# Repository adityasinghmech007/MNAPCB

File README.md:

# STM32-Based Motor Control PCB

## 📌 Overview

This project is a custom-designed 2-layer motor control PCB developed for embedded motion control and automation applications. The board integrates an STM32 microcontroller, motor driver circuitry, INA226 current sensing, and onboard power management for efficient and reliable motor control.

The PCB was designed to support real-time motor actuation, current monitoring, and embedded control workflows for robotics and mechatronics systems.

---

## 🚀 Features

* STM32-based embedded control system
* Integrated motor driver interface for DC/Stepper motor control
* INA226 current and voltage monitoring
* Onboard DC power regulation circuitry
* Multi-voltage power distribution architecture
* 2-layer PCB optimized for compact routing and manufacturability
* Support for sensor interfacing and external peripherals
* Designed for rapid prototyping and embedded testing applications

---

## 🔧 Hardware Components

### Microcontroller

* STM32 MCU for real-time motor control and peripheral interfacing

### Current Sensing

* INA226 current/voltage monitoring IC
* I2C communication interface

### Motor Control

* Motor driver integration for controlling motors
* PWM and direction-based control signals

### Power Management

* DC-DC conversion stages for generating required operating voltages
* Power filtering and decoupling circuitry
* Separate logic and motor power domains

---

## 🛠️ PCB Design Details

* 2-layer PCB design
* Optimized power and signal routing
* Ground plane implementation for noise reduction
* Compact component placement for efficient thermal and electrical performance
* Designed using standard PCB CAD tools

---

## 💻 Firmware & Embedded Features

* STM32 HAL-based firmware development
* PWM motor control
* Current monitoring using INA226
* GPIO, I2C, UART, and timer peripheral integration
* Real-time control and debugging support

---

## 📷 Project Highlights

* Complete schematic and PCB design from scratch
* Integrated power electronics and embedded control on a single board
* Focus on reliability, modularity, and rapid hardware iteration
* Suitable for robotics, automation, and mechatronics applications

---

## 🔩 Applications

* Robotics platforms
* Motor control systems
* Embedded automation
* Mechatronics prototyping
* Industrial testing systems

---

## 📚 Technologies Used

* STM32
* Embedded C
* PCB Design
* Power Electronics
* INA226
* Motor Drivers
* I2C Communication
* PWM Control

---

Built with a strong focus on practical embedded engineering, hardware integration, and real-world motion control applications.

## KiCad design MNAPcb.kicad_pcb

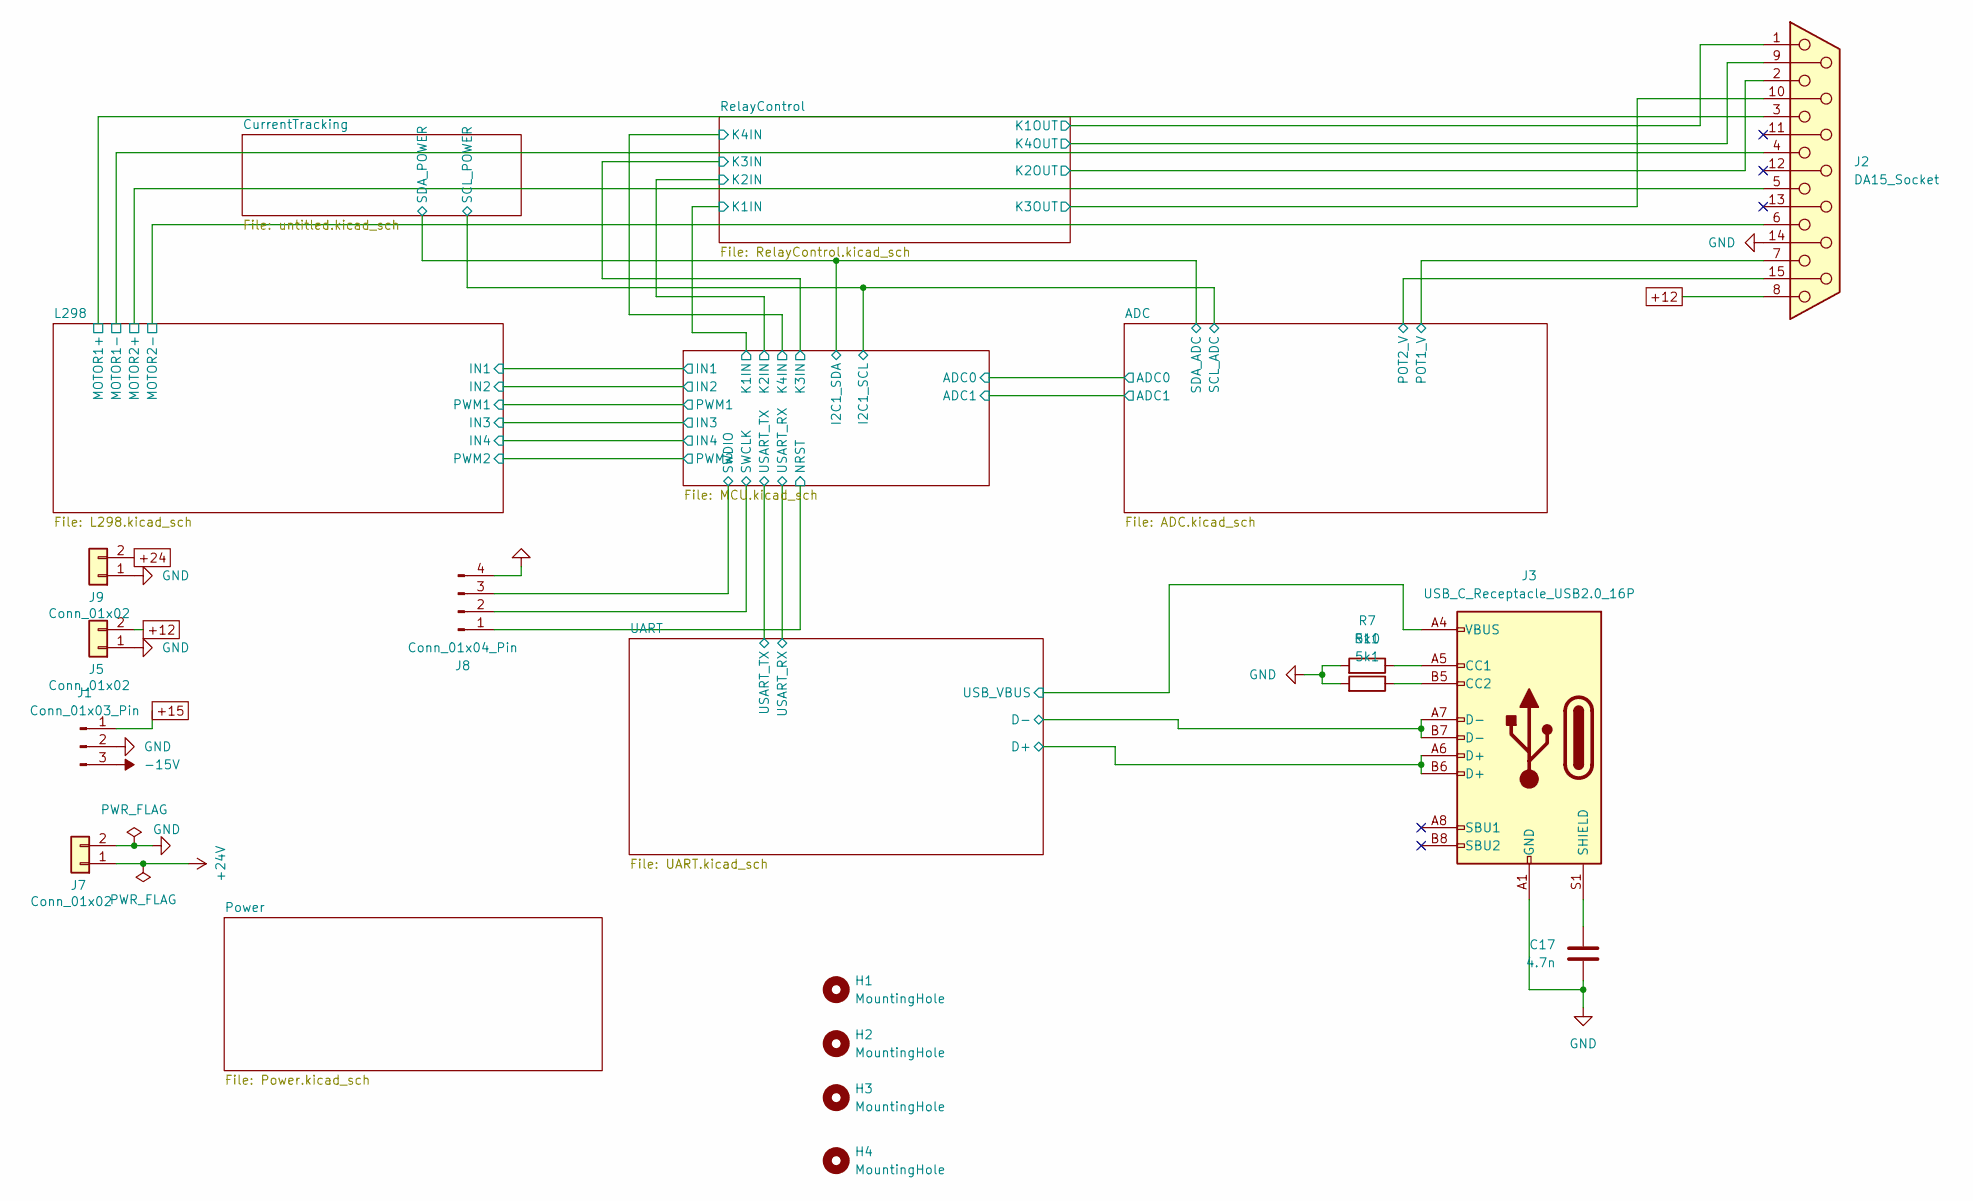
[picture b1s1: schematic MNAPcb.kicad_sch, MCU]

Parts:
C17: 4.7n; C_0805_2012Metric_Pad1.18x1.45mm_HandSolder
H1, H2, H3, H4: MountingHole; MountingHole_3.2mm_M3_DIN965
J1: Conn_01x03_Pin; Molex_KK-254_AE-6410-03A_1x03_P2.54mm_Vertical
J2: DA15_Socket; DSUB-15_Socket_Horizontal_P2.77x2.54mm_EdgePinOffset9.40mm
J3: USB_C_Receptacle_USB2.0_16P; USB_C_Receptacle_Palconn_UTC16-G
J5, J7, J9: Conn_01x02; TE_826576-2_1x02_P3.96mm_Vertical
J8: Conn_01x04_Pin; JST_EH_B4B-EH-A_1x04_P2.50mm_Vertical
R7, R10: 5k1; R_0805_2012Metric_Pad1.20x1.40mm_HandSolder

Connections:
+12: J2.8, J5.2; also elsewhere on the board
+15: J1.1; also elsewhere on the board
+24: J9.2; also elsewhere on the board
+24V: J7.1; also elsewhere on the board
-15V: J1.3; also elsewhere on the board
/ADC/POT1_V: J2.7; also elsewhere on the board
/ADC/POT2_V: J2.15; also elsewhere on the board
/L298/MOTOR1+: J2.3; also elsewhere on the board
/L298/MOTOR1-: J2.4; also elsewhere on the board
/L298/MOTOR2+: J2.5; also elsewhere on the board
/L298/MOTOR2-: J2.6; also elsewhere on the board
/MCU/NRST: J8.1; also elsewhere on the board
/MCU/SWCLK: J8.2; also elsewhere on the board
/MCU/SWDIO: J8.3; also elsewhere on the board
/RelayControl/K1OUT: J2.1; also elsewhere on the board
/RelayControl/K2OUT: J2.2; also elsewhere on the board
/RelayControl/K3OUT: J2.10; also elsewhere on the board
/RelayControl/K4OUT: J2.9; also elsewhere on the board
/UART/D+: J3.A6 (D+), J3.B6 (D+); also elsewhere on the board
/UART/D-: J3.A7 (D-), J3.B7 (D-); also elsewhere on the board
/UART/USB_VBUS: J3.A4 (VBUS), J3.A9 (VBUS), J3.B4 (VBUS), J3.B9 (VBUS); also elsewhere on the board
GND: C17.2, J1.2, J2.14, J3.A1 (GND), J3.A12 (GND), J3.B1 (GND), J3.B12 (GND), J5.1, J7.2, J8.4, J9.1, R7.2, R10.2; also elsewhere on the board
unnamed: J3.A5 (CC1), R7.1
unnamed: J3.B5 (CC2), R10.1
unnamed: C17.1, J3.S1 (SHIELD)

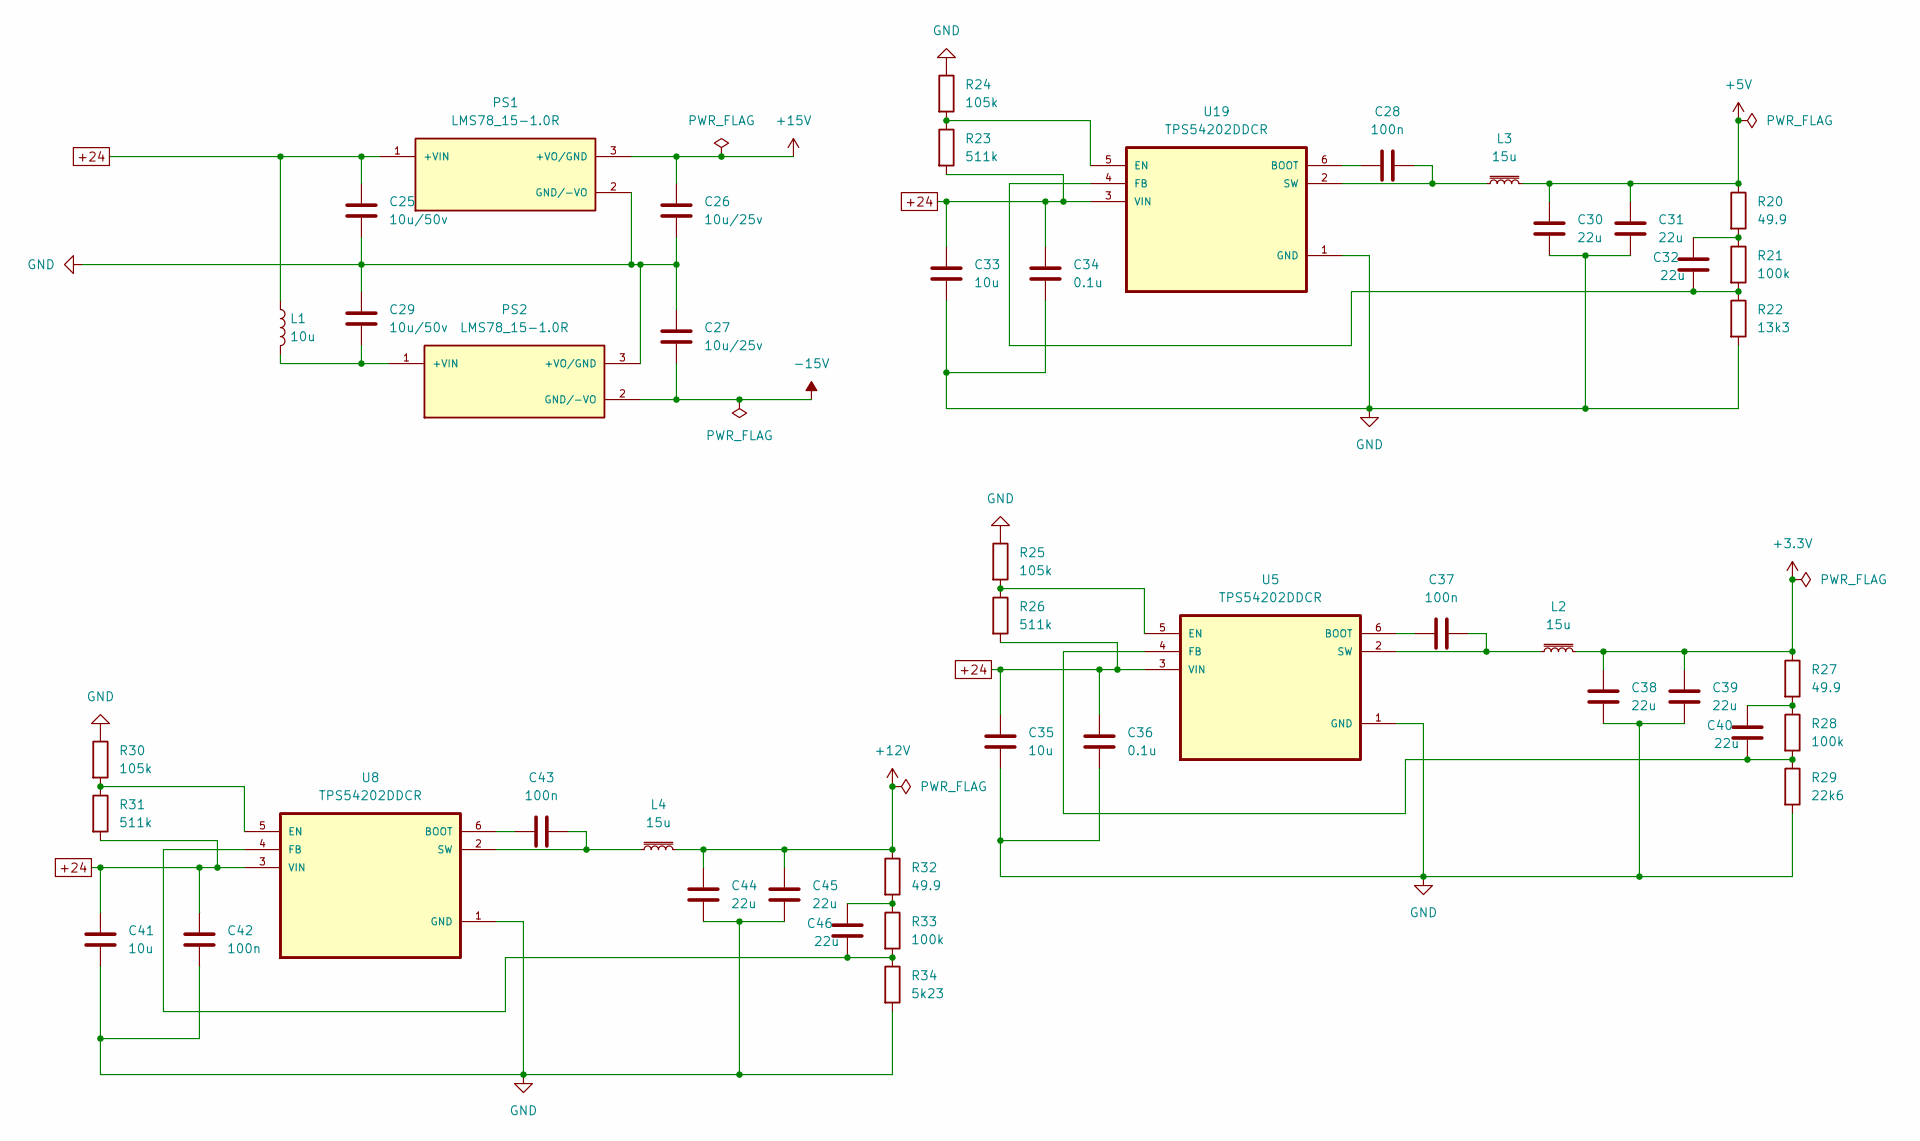
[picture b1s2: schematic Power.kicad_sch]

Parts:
C25, C29: 10u/50v; C_1210_3225Metric_Pad1.33x2.70mm_HandSolder
C26, C27: 10u/25v; C_1210_3225Metric_Pad1.33x2.70mm_HandSolder
C28, C37, C42, C43: 100n; C_0805_2012Metric_Pad1.18x1.45mm_HandSolder
C30, C31, C32, C38, C39, C40, C44, C45, C46: 22u; C_1210_3225Metric_Pad1.33x2.70mm_HandSolder
C33, C35, C41: 10u; C_1206_3216Metric_Pad1.33x1.80mm_HandSolder
C34, C36: 0.1u; C_0805_2012Metric_Pad1.18x1.45mm_HandSolder
L1: 10u; L_1210_3225Metric_Pad1.42x2.65mm_HandSolder
L2, L3, L4: 15u; L_1210_3225Metric_Pad1.42x2.65mm_HandSolder
PS1, PS2: LMS78_15-1.0R; CONV_LMS78_15-1.0R; PARTREV 2023-1.3
R20, R27, R32: 49.9; R_0805_2012Metric_Pad1.20x1.40mm_HandSolder
R21, R28, R33: 100k; R_0805_2012Metric_Pad1.20x1.40mm_HandSolder
R22: 13k3; R_0805_2012Metric_Pad1.20x1.40mm_HandSolder
R23, R26, R31: 511k; R_0805_2012Metric_Pad1.20x1.40mm_HandSolder
R24, R25, R30: 105k; R_0805_2012Metric_Pad1.20x1.40mm_HandSolder
R29: 22k6; R_0805_2012Metric_Pad1.20x1.40mm_HandSolder
R34: 5k23; R_0805_2012Metric_Pad1.20x1.40mm_HandSolder
U5, U8, U19: TPS54202DDCR; SOT95P280X110-6N

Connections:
+3.3V: C38.1, C39.1, L2.2, R27.1; also elsewhere on the board
+5V: C30.1, C31.1, L3.2, R20.1; also elsewhere on the board
+12V: C44.1, C45.1, L4.2, R32.1; also elsewhere on the board
+15V: C26.1, PS1.3 (+VO/GND); also elsewhere on the board
+24: C25.1, C33.1, C34.1, C35.1, C36.1, C41.1, C42.1, L1.1, PS1.1 (+VIN), R23.2, R26.2, R31.2, U5.3 (VIN), U8.3 (VIN), U19.3 (VIN); also elsewhere on the board
-15V: C27.2, PS2.2 (GND/-VO); also elsewhere on the board
GND: C25.2, C26.2, C27.1, C29.1, C30.2, C31.2, C33.2, C34.2, C35.2, C36.2, C38.2, C39.2, C41.2, C42.2, C44.2, C45.2, PS1.2 (GND/-VO), PS2.3 (+VO/GND), R22.2, R24.1, R25.1, R29.2, R30.1, R34.2, U5.1 (GND), U8.1 (GND), U19.1 (GND); also elsewhere on the board
unnamed: C32.1, R20.2, R21.1
unnamed: C40.1, R27.2, R28.1
unnamed: C46.1, R32.2, R33.1
unnamed: C29.2, L1.2, PS2.1 (+VIN)
unnamed: C37.1, U5.6 (BOOT)
unnamed: R25.2, R26.1, U5.5 (EN)
unnamed: C40.2, R28.2, R29.1, U5.4 (FB)
unnamed: C37.2, L2.1, U5.2 (SW)
unnamed: C43.1, U8.6 (BOOT)
unnamed: R30.2, R31.1, U8.5 (EN)
unnamed: C46.2, R33.2, R34.1, U8.4 (FB)
unnamed: C43.2, L4.1, U8.2 (SW)
unnamed: C28.1, U19.6 (BOOT)
unnamed: R23.1, R24.2, U19.5 (EN)
unnamed: C32.2, R21.2, R22.1, U19.4 (FB)
unnamed: C28.2, L3.1, U19.2 (SW)

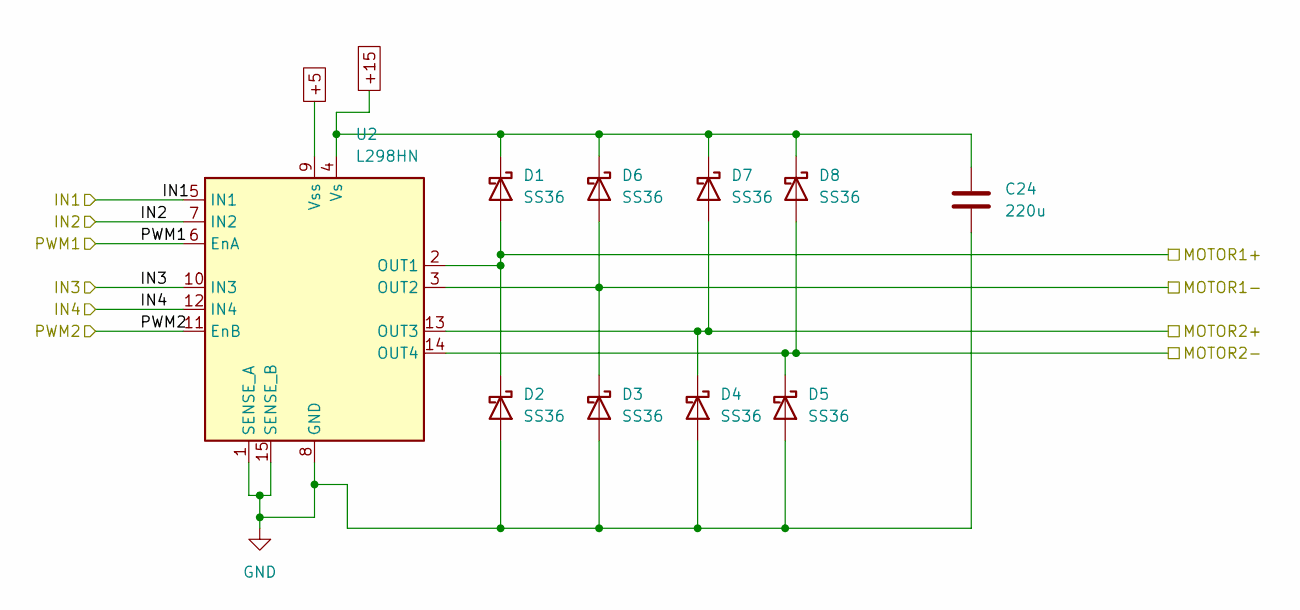
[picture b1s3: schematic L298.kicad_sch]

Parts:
C24: 220u; CP_Radial_D5.0mm_P2.00mm
D1, D2, D3, D4, D5, D6, D7, D8: SS36; D_SMA_Handsoldering
U2: L298HN; TO-220-15_P2.54x5.08mm_StaggerEven_Lead4.58mm_Vertical

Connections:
+5: U2.9 (Vss); also elsewhere on the board
+15: C24.1, D1.1 (K), D6.1 (K), D7.1 (K), D8.1 (K), U2.4 (Vs); also elsewhere on the board
/L298/IN1: U2.5 (IN1); also elsewhere on the board
/L298/IN2: U2.7 (IN2); also elsewhere on the board
/L298/IN3: U2.10 (IN3); also elsewhere on the board
/L298/IN4: U2.12 (IN4); also elsewhere on the board
/L298/MOTOR1+: D1.2 (A), D2.1 (K), U2.2 (OUT1); also elsewhere on the board
/L298/MOTOR1-: D3.1 (K), D6.2 (A), U2.3 (OUT2); also elsewhere on the board
/L298/MOTOR2+: D4.1 (K), D7.2 (A), U2.13 (OUT3); also elsewhere on the board
/L298/MOTOR2-: D5.1 (K), D8.2 (A), U2.14 (OUT4); also elsewhere on the board
/L298/PWM1: U2.6 (EnA); also elsewhere on the board
/L298/PWM2: U2.11 (EnB); also elsewhere on the board
GND: C24.2, D2.2 (A), D3.2 (A), D4.2 (A), D5.2 (A), U2.1 (SENSE_A), U2.8 (GND), U2.15 (SENSE_B); also elsewhere on the board

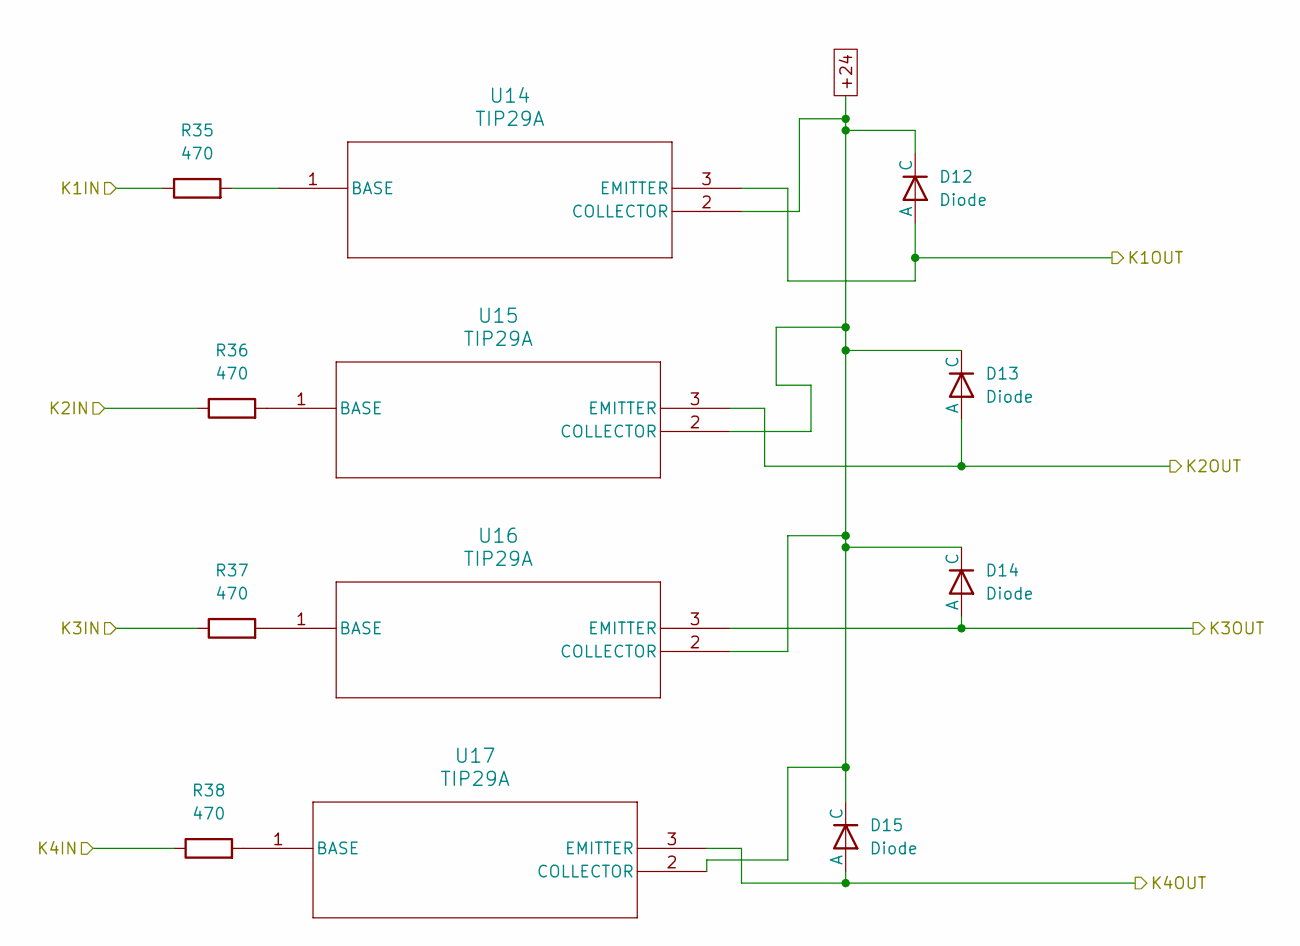
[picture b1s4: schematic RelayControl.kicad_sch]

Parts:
D12, D13, D14, D15: Diode; D_0805_2012Metric_Pad1.15x1.40mm_HandSolder
R35, R36, R37, R38: 470; R_0805_2012Metric
U14, U15, U16, U17: TIP29A; TO-220AB_ONS

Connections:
+24: D12.2 (C), D13.2 (C), D14.2 (C), D15.2 (C), U14.2 (COLLECTOR), U15.2 (COLLECTOR), U16.2 (COLLECTOR), U17.2 (COLLECTOR); also elsewhere on the board
/MCU/K1IN: R35.1; also elsewhere on the board
/MCU/K2IN: R36.1; also elsewhere on the board
/MCU/K3IN: R37.1; also elsewhere on the board
/MCU/K4IN: R38.1; also elsewhere on the board
/RelayControl/K1OUT: D12.1 (A), U14.3 (EMITTER); also elsewhere on the board
/RelayControl/K2OUT: D13.1 (A), U15.3 (EMITTER); also elsewhere on the board
/RelayControl/K3OUT: D14.1 (A), U16.3 (EMITTER); also elsewhere on the board
/RelayControl/K4OUT: D15.1 (A), U17.3 (EMITTER); also elsewhere on the board
unnamed: R35.2, U14.1 (BASE)
unnamed: R36.2, U15.1 (BASE)
unnamed: R37.2, U16.1 (BASE)
unnamed: R38.2, U17.1 (BASE)

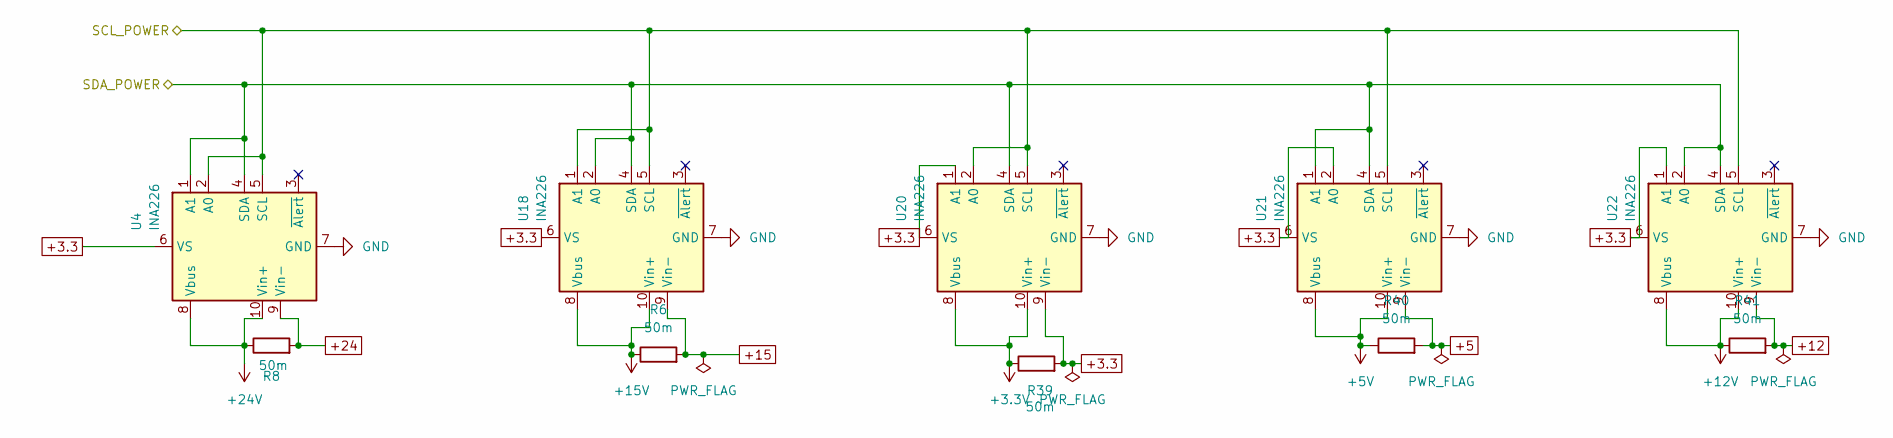
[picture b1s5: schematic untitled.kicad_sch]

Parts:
R6, R8, R39, R40, R41: 50m; R_2512_6332Metric_Pad1.40x3.35mm_HandSolder
U4, U18, U20, U21, U22: INA226; VSSOP-10_3x3mm_P0.5mm

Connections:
+3.3: R39.2, U4.6 (VS), U18.6 (VS), U20.1 (A1), U20.6 (VS), U20.9 (Vin-), U21.2 (A0), U21.6 (VS), U22.1 (A1), U22.6 (VS); also elsewhere on the board
+3.3V: R39.1, U20.8 (Vbus), U20.10 (Vin+); also elsewhere on the board
+5: R40.2, U21.9 (Vin-); also elsewhere on the board
+5V: R40.1, U21.8 (Vbus), U21.10 (Vin+); also elsewhere on the board
+12: R41.2, U22.9 (Vin-); also elsewhere on the board
+12V: R41.1, U22.8 (Vbus), U22.10 (Vin+); also elsewhere on the board
+15: R6.2, U18.9 (Vin-); also elsewhere on the board
+15V: R6.1, U18.8 (Vbus), U18.10 (Vin+); also elsewhere on the board
+24: R8.2, U4.9 (Vin-); also elsewhere on the board
+24V: R8.1, U4.8 (Vbus), U4.10 (Vin+); also elsewhere on the board
/ADC/SCL_ADC: U4.2 (A0), U4.5 (SCL), U18.1 (A1), U18.5 (SCL), U20.2 (A0), U20.5 (SCL), U21.5 (SCL), U22.5 (SCL); also elsewhere on the board
/ADC/SDA_ADC: U4.1 (A1), U4.4 (SDA), U18.2 (A0), U18.4 (SDA), U20.4 (SDA), U21.1 (A1), U21.4 (SDA), U22.2 (A0), U22.4 (SDA); also elsewhere on the board
GND: U4.7 (GND), U18.7 (GND), U20.7 (GND), U21.7 (GND), U22.7 (GND); also elsewhere on the board

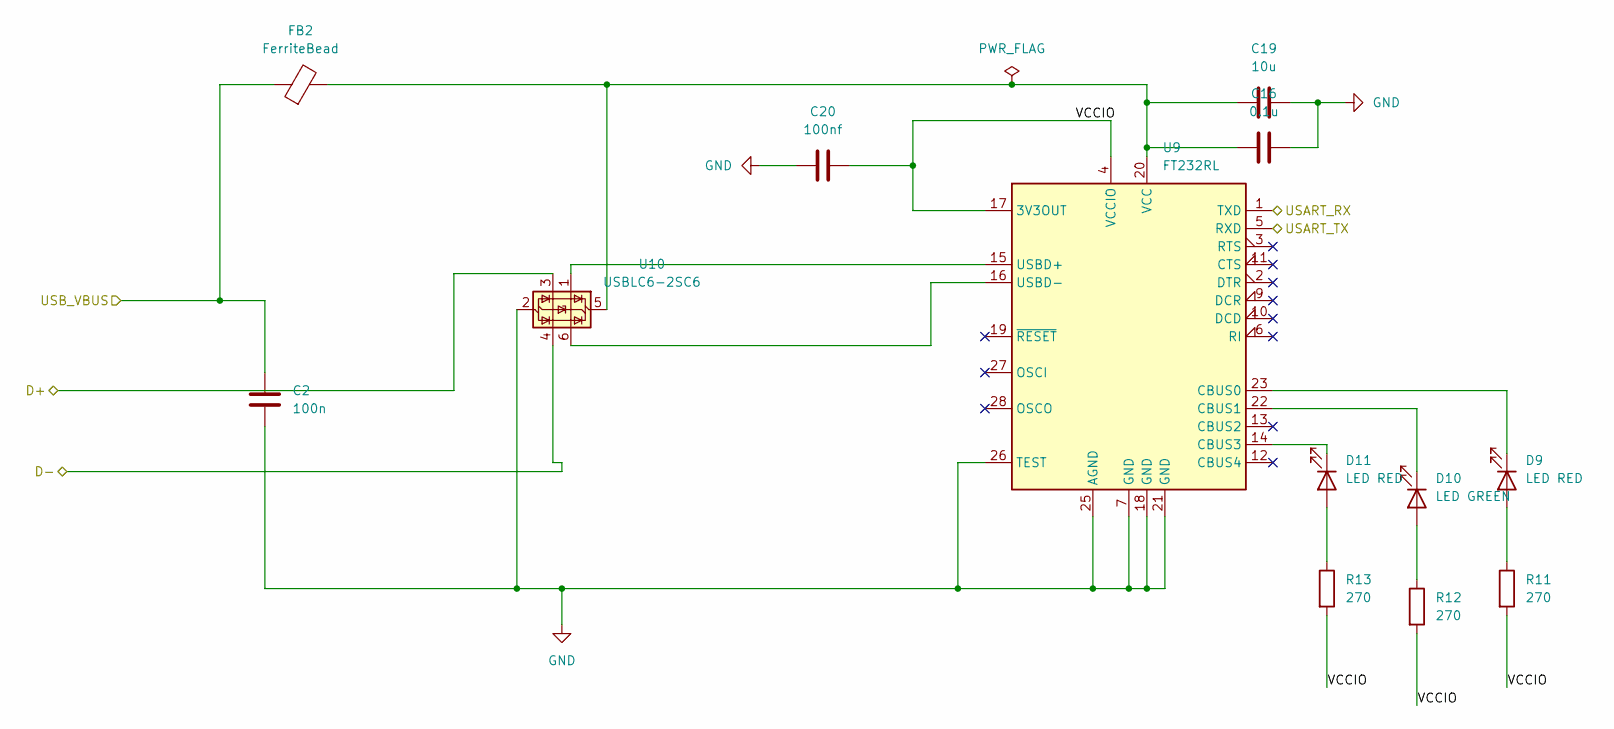
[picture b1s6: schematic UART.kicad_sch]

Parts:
C2: 100n; C_0805_2012Metric_Pad1.18x1.45mm_HandSolder
C16: 0.1u; C_0805_2012Metric_Pad1.18x1.45mm_HandSolder
C19: 10u; C_1206_3216Metric_Pad1.33x1.80mm_HandSolder
C20: 100nf; C_0805_2012Metric_Pad1.18x1.45mm_HandSolder
D9, D11: LED RED; LED_0805_2012Metric_Pad1.15x1.40mm_HandSolder
D10: LED GREEN; LED_0805_2012Metric_Pad1.15x1.40mm_HandSolder
FB2: FerriteBead; L_0805_2012Metric_Pad1.15x1.40mm_HandSolder
R11, R12, R13: 270; R_0805_2012Metric_Pad1.20x1.40mm_HandSolder
U9: FT232RL; SSOP-28_5.3x10.2mm_P0.65mm
U10: USBLC6-2SC6; SOT-23-6

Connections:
/MCU/USART_RX: U9.1 (TXD); also elsewhere on the board
/MCU/USART_TX: U9.5 (RXD); also elsewhere on the board
/UART/D+: U10.3 (I/O2); also elsewhere on the board
/UART/D-: U10.4 (I/O2); also elsewhere on the board
/UART/USB_VBUS: C2.1, FB2.1; also elsewhere on the board
/UART/VCCIO: C20.1, R11.2, R12.2, R13.2, U9.4 (VCCIO), U9.17 (3V3OUT)
GND: C2.2, C16.1, C19.1, C20.2, U9.7 (GND), U9.18 (GND), U9.21 (GND), U9.25 (AGND), U9.26 (TEST), U10.2 (GND); also elsewhere on the board
unnamed: D9.2 (A), R11.1
unnamed: D9.1 (K), U9.23 (CBUS0)
unnamed: D10.2 (A), R12.1
unnamed: D10.1 (K), U9.22 (CBUS1)
unnamed: D11.2 (A), R13.1
unnamed: D11.1 (K), U9.14 (CBUS3)
unnamed: U9.15 (USBD+), U10.1 (I/O1)
unnamed: U9.16 (USBD-), U10.6 (I/O1)
unnamed: C16.2, C19.2, FB2.2, U9.20 (VCC), U10.5 (VBUS)

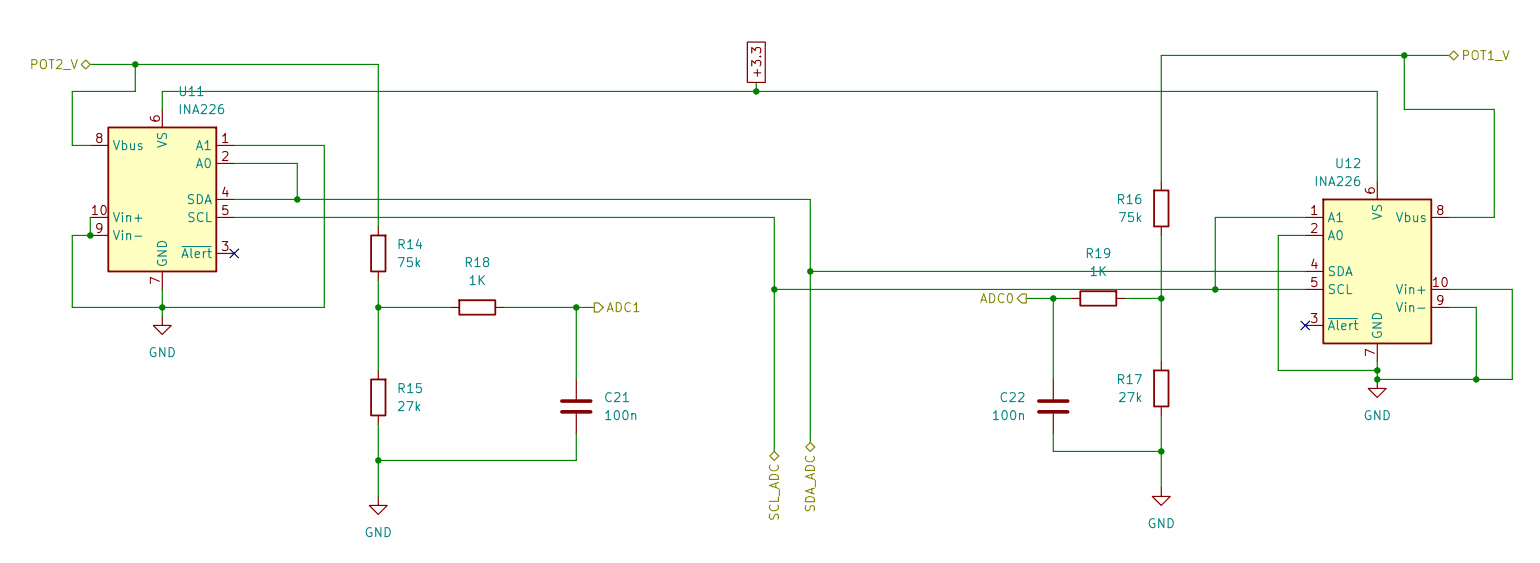
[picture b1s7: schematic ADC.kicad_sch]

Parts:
C21, C22: 100n; C_0805_2012Metric_Pad1.18x1.45mm_HandSolder
R14, R16: 75k; R_0805_2012Metric_Pad1.20x1.40mm_HandSolder
R15, R17: 27k; R_0805_2012Metric_Pad1.20x1.40mm_HandSolder
R18, R19: 1K; R_0805_2012Metric_Pad1.20x1.40mm_HandSolder
U11, U12: INA226; VSSOP-10_3x3mm_P0.5mm

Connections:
+3.3: U11.6 (VS), U12.6 (VS); also elsewhere on the board
/ADC/ADC0: C22.1, R19.1; also elsewhere on the board
/ADC/ADC1: C21.1, R18.1; also elsewhere on the board
/ADC/POT1_V: R16.2, U12.8 (Vbus); also elsewhere on the board
/ADC/POT2_V: R14.2, U11.8 (Vbus); also elsewhere on the board
/ADC/SCL_ADC: U11.5 (SCL), U12.1 (A1), U12.5 (SCL); also elsewhere on the board
/ADC/SDA_ADC: U11.2 (A0), U11.4 (SDA), U12.4 (SDA); also elsewhere on the board
GND: C21.2, C22.2, R15.1, R17.1, U11.1 (A1), U11.7 (GND), U11.9 (Vin-), U11.10 (Vin+), U12.2 (A0), U12.7 (GND), U12.9 (Vin-), U12.10 (Vin+); also elsewhere on the board
unnamed: R14.1, R15.2, R18.2
unnamed: R16.1, R17.2, R19.2

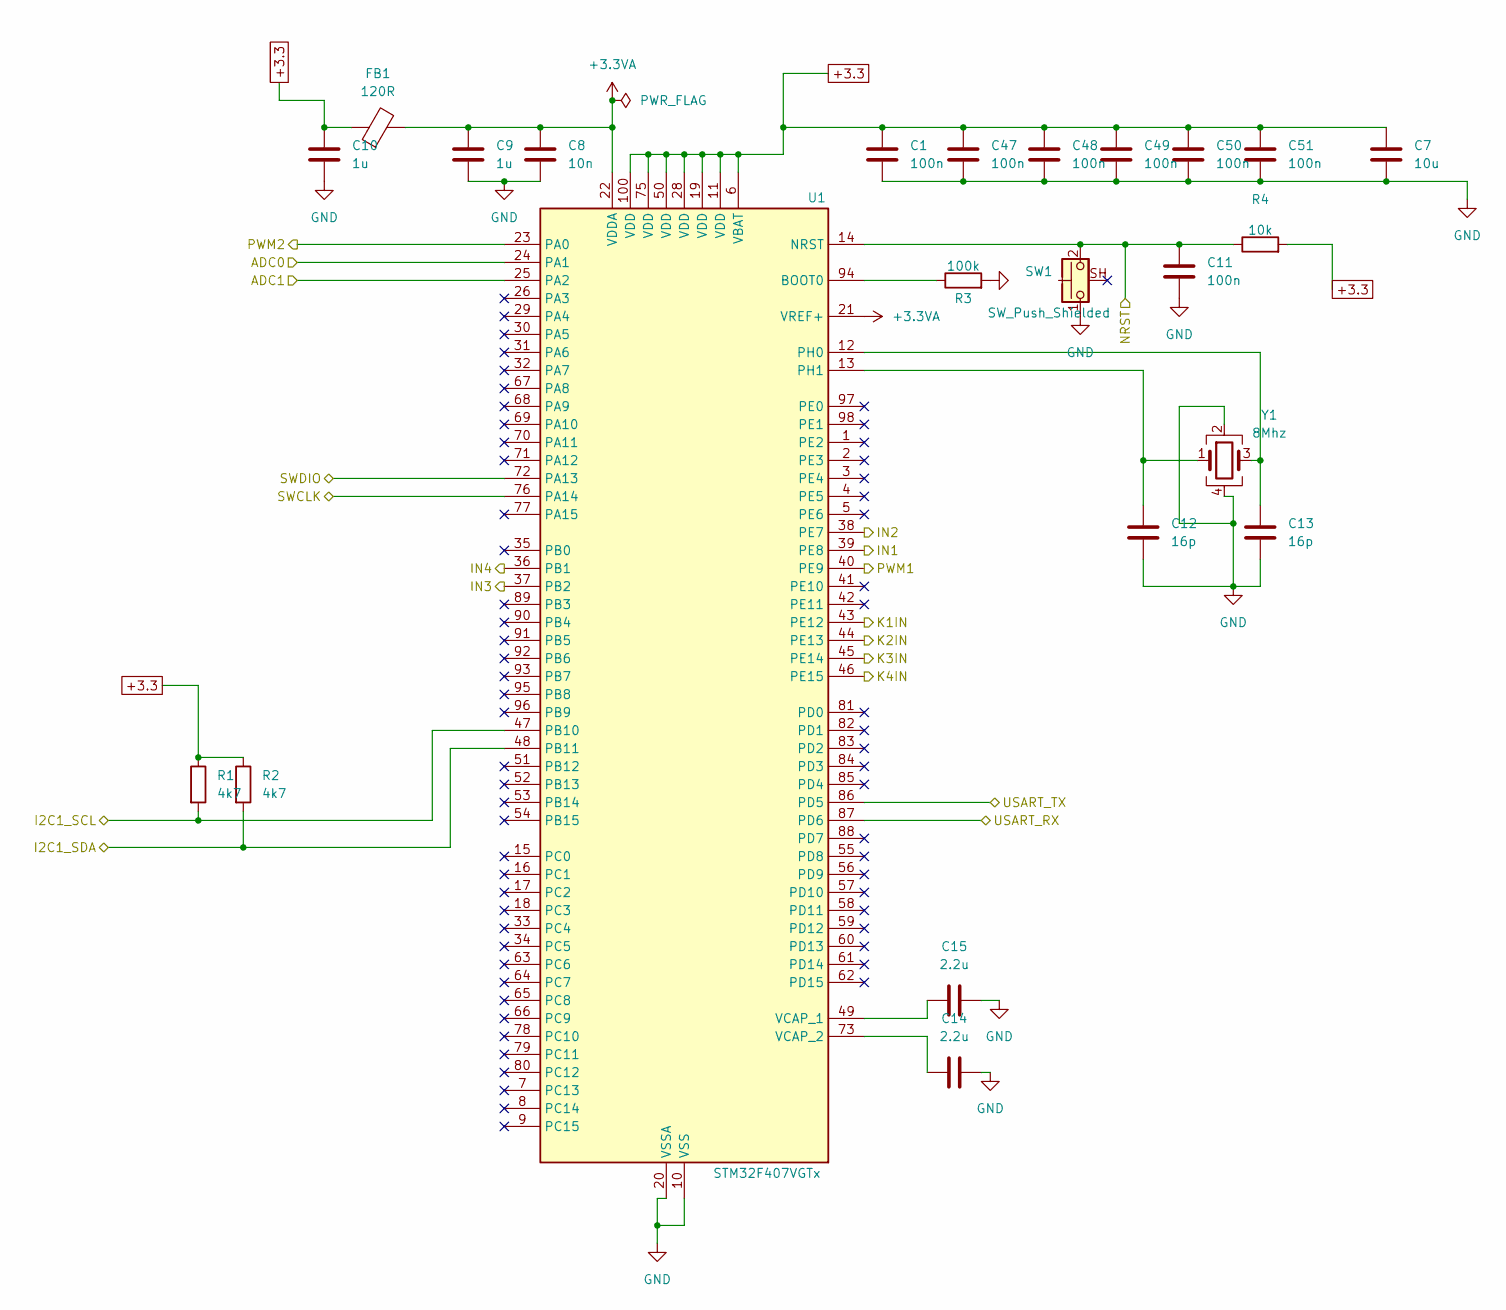
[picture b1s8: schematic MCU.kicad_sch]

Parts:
C1, C11, C47, C48, C49, C50, C51: 100n; C_0805_2012Metric_Pad1.18x1.45mm_HandSolder
C7: 10u; C_1206_3216Metric_Pad1.33x1.80mm_HandSolder
C8: 10n; C_0603_1608Metric_Pad1.08x0.95mm_HandSolder
C9, C10: 1u; C_1206_3216Metric_Pad1.33x1.80mm_HandSolder
C12, C13: 16p; C_0603_1608Metric_Pad1.08x0.95mm_HandSolder
C14: 2.2u; C_0603_1608Metric_Pad1.08x0.95mm_HandSolder
C15: 2.2u; C_0805_2012Metric_Pad1.18x1.45mm_HandSolder
FB1: 120R; L_0603_1608Metric_Pad1.05x0.95mm_HandSolder
R1, R2: 4k7; R_1225_3264Metric_Pad1.47x6.45mm_HandSolder
R3: 100k; R_0805_2012Metric_Pad1.20x1.40mm_HandSolder
R4: 10k; R_0805_2012Metric_Pad1.20x1.40mm_HandSolder
SW1: SW_Push_Shielded; SW_PUSH_6mm_H7.3mm
U1: STM32F407VGTx; LQFP-100_14x14mm_P0.5mm
Y1: 8Mhz; Crystal_HC33-U_Vertical

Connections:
+3.3: C1.1, C7.1, C10.1, C47.1, C48.1, C49.1, C50.1, C51.1, FB1.1, R1.1, R2.1, R4.2, U1.6 (VBAT), U1.11 (VDD), U1.19 (VDD), U1.28 (VDD), U1.50 (VDD), U1.75 (VDD), U1.100 (VDD); also elsewhere on the board
+3.3VA: C8.1, C9.1, FB1.2, U1.21 (VREF+), U1.22 (VDDA)
/ADC/ADC0: U1.24 (PA1); also elsewhere on the board
/ADC/ADC1: U1.25 (PA2); also elsewhere on the board
/ADC/SCL_ADC: R1.2, U1.47 (PB10); also elsewhere on the board
/ADC/SDA_ADC: R2.2, U1.48 (PB11); also elsewhere on the board
/L298/IN1: U1.39 (PE8); also elsewhere on the board
/L298/IN2: U1.38 (PE7); also elsewhere on the board
/L298/IN3: U1.37 (PB2); also elsewhere on the board
/L298/IN4: U1.36 (PB1); also elsewhere on the board
/L298/PWM1: U1.40 (PE9); also elsewhere on the board
/L298/PWM2: U1.23 (PA0); also elsewhere on the board
/MCU/K1IN: U1.43 (PE12); also elsewhere on the board
/MCU/K2IN: U1.44 (PE13); also elsewhere on the board
/MCU/K3IN: U1.45 (PE14); also elsewhere on the board
/MCU/K4IN: U1.46 (PE15); also elsewhere on the board
/MCU/NRST: C11.1, R4.1, SW1.2, U1.14 (NRST); also elsewhere on the board
/MCU/SWCLK: U1.76 (PA14); also elsewhere on the board
/MCU/SWDIO: U1.72 (PA13); also elsewhere on the board
/MCU/USART_RX: U1.87 (PD6); also elsewhere on the board
/MCU/USART_TX: U1.86 (PD5); also elsewhere on the board
GND: C1.2, C7.2, C8.2, C9.2, C10.2, C11.2, C12.2, C13.2, C14.2, C15.1, C47.2, C48.2, C49.2, C50.2, C51.2, R3.2, SW1.1, U1.10 (VSS), U1.20 (VSSA), U1.27 (VSS), U1.74 (VSS), U1.99 (VSS), Y1.2, Y1.4; also elsewhere on the board
unnamed: R3.1, U1.94 (BOOT0)
unnamed: C13.1, U1.12 (PH0), Y1.3
unnamed: C12.1, U1.13 (PH1), Y1.1
unnamed: C15.2, U1.49 (VCAP_1)
unnamed: C14.1, U1.73 (VCAP_2)

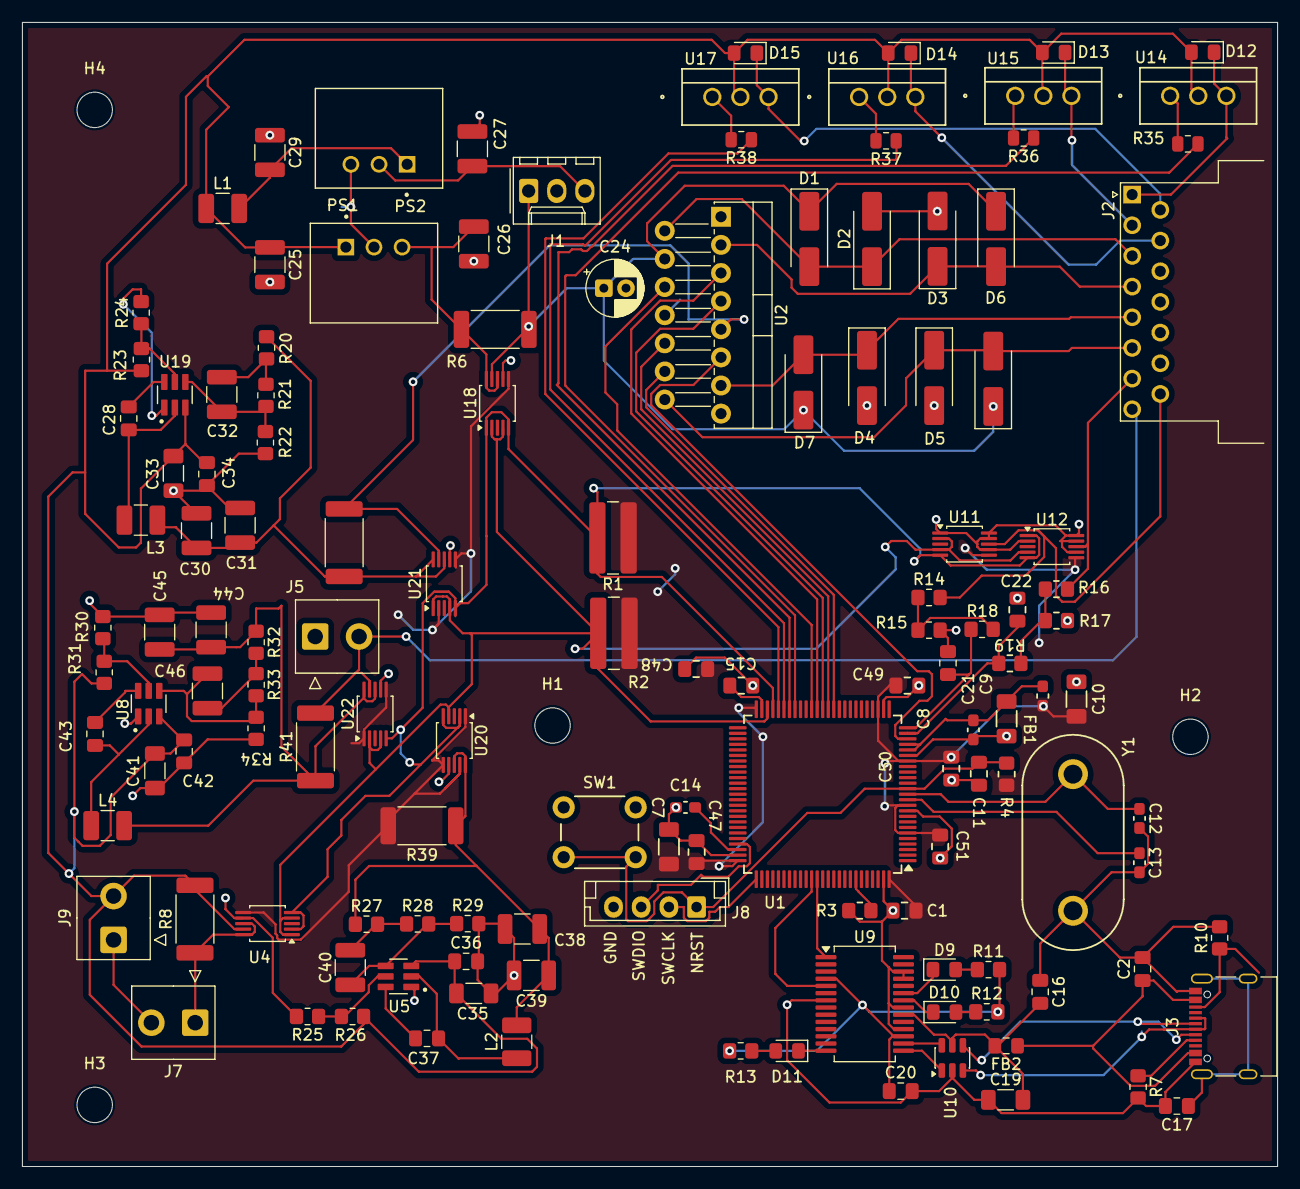
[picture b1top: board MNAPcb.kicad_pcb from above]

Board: 2 copper layers, 113.4 x 103.3 mm, 138 parts (0 on the bottom side), 85 nets.

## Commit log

2025-10-21 Initial Commit of Kicad Project
2025-10-22 Added Footprint
2025-10-22 Changes to footprint
2025-11-02 Added a Relay Circuit
2026-02-01 Solved errors
2026-03-19 New PCB Changes
2026-03-22 FInal Changes in Schgematic
2026-03-25 Made Changes to Layout and USB C
2026-03-26 Fixed the Silkscreen issue
2026-04-01 Deleted Uneeded Portion
2026-04-02 Used Zones and Net
2026-04-04 Solved all the Erros
2026-05-30 Add README for STM32-Based Motor Control PCB
    Added detailed project overview, features, hardware components, PCB design details, firmware features, project highlights, applications, and technologies used for the STM32-based motor control PCB.
